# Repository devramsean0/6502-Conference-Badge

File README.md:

# 6502-Conference-Badge
A little 6502 flashy LED conference badge

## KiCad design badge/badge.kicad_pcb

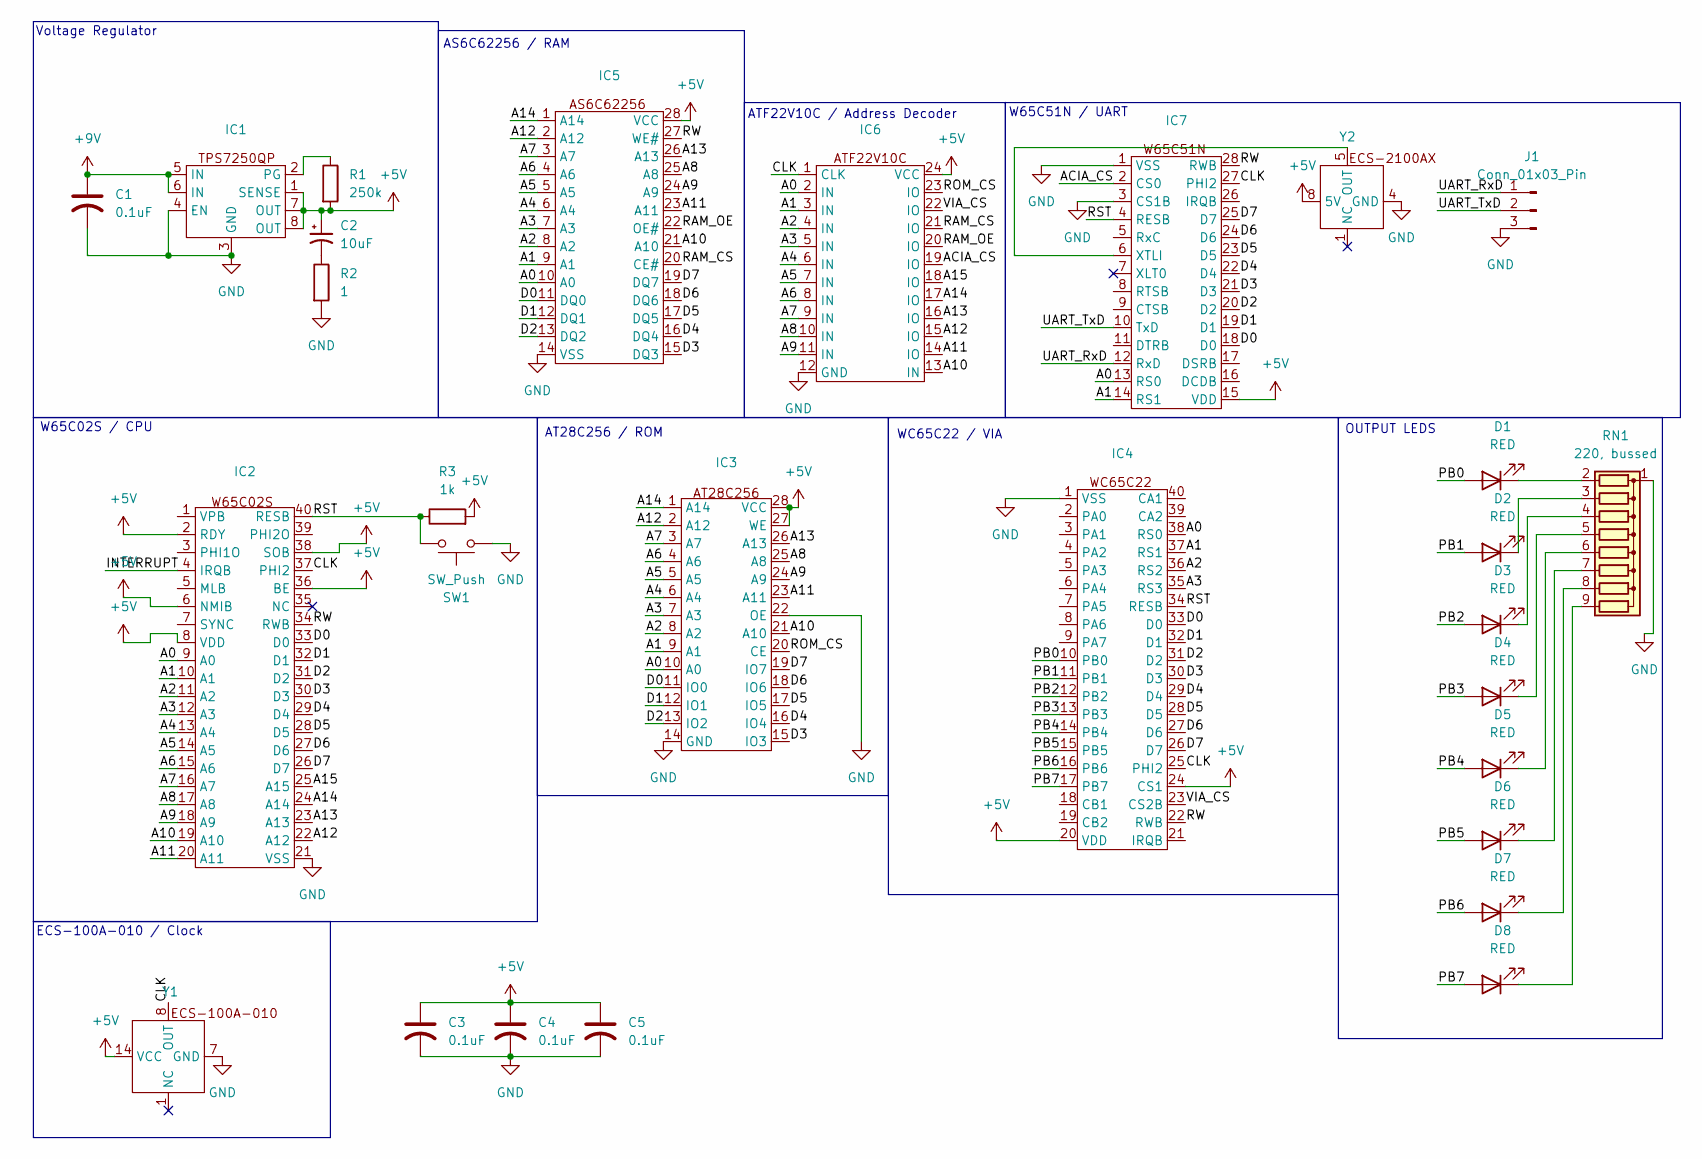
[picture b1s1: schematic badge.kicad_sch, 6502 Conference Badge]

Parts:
C1, C3, C4, C5: 0.1uF; CP_Radial_Tantal_D5.5mm_P2.50mm
C2: 10uF; CP_Axial_L10.0mm_D6.0mm_P15.00mm_Horizontal
D1, D2, D3, D4, D5, D6, D7, D8: RED; LED_D5.0mm
IC1: DIP-8_W7.62mm_Socket
IC2, IC4: DIP-40_W15.24mm_Socket
IC3, IC5, IC7: DIP-28_W15.24mm_Socket
IC6: DIP-24_W7.62mm_Socket
J1: Conn_01x03_Pin; PinHeader_1x03_P2.54mm_Vertical
R1: 250k; R_Axial_DIN0411_L9.9mm_D3.6mm_P7.62mm_Vertical
R2: 1; R_Axial_DIN0516_L15.5mm_D5.0mm_P20.32mm_Horizontal
R3: 1k; R_Axial_DIN0309_L9.0mm_D3.2mm_P12.70mm_Horizontal
RN1: 220, bussed; R_Array_SIP9
SW1: SW_Push; SW_PUSH_6mm
Y1: ECS100A010
Y2: ECS2100AX18432MHZ

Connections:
+9V: C1.1, IC1.5 (IN), IC1.6 (IN)
/A0: IC2.9 (A0), IC3.10 (A0), IC4.38 (RS0), IC5.10 (A0), IC6.2 (IN), IC7.13 (RS0)
/A1: IC2.10 (A1), IC3.9 (A1), IC4.37 (RS1), IC5.9 (A1), IC6.3 (IN), IC7.14 (RS1)
/A2: IC2.11 (A2), IC3.8 (A2), IC4.36 (RS2), IC5.8 (A2), IC6.4 (IN)
/A3: IC2.12 (A3), IC3.7 (A3), IC4.35 (RS3), IC5.7 (A3), IC6.5 (IN)
/A4: IC2.13 (A4), IC3.6 (A4), IC5.6 (A4), IC6.6 (IN)
/A5: IC2.14 (A5), IC3.5 (A5), IC5.5 (A5), IC6.7 (IN)
/A6: IC2.15 (A6), IC3.4 (A6), IC5.4 (A6), IC6.8 (IN)
/A7: IC2.16 (A7), IC3.3 (A7), IC5.3 (A7), IC6.9 (IN)
/A8: IC2.17 (A8), IC3.25 (A8), IC5.25 (A8), IC6.10 (IN)
/A9: IC2.18 (A9), IC3.24 (A9), IC5.24 (A9), IC6.11 (IN)
/A10: IC2.19 (A10), IC3.21 (A10), IC5.21 (A10), IC6.13 (IN)
/A11: IC2.20 (A11), IC3.23 (A11), IC5.23 (A11), IC6.14 (IO)
/A12: IC2.22 (A12), IC3.2 (A12), IC5.2 (A12), IC6.15 (IO)
/A14: IC2.24 (A14), IC3.1 (A14), IC5.1 (A14), IC6.17 (IO)
/A15: IC2.25 (A15), IC6.18 (IO)
/ACIA_CS: IC6.19 (IO), IC7.2 (CS0)
/CLK: IC2.37 (PHI2), IC4.25 (PHI2), IC6.1 (CLK), IC7.27 (PHI2), Y1.8 (OUT)
/D0: IC2.33 (D0), IC3.11 (IO0), IC4.33 (D0), IC5.11 (DQ0), IC7.18 (D0)
/D1: IC2.32 (D1), IC3.12 (IO1), IC4.32 (D1), IC5.12 (DQ1), IC7.19 (D1)
/D2: IC2.31 (D2), IC3.13 (IO2), IC4.31 (D2), IC5.13 (DQ2), IC7.20 (D2)
/D3: IC2.30 (D3), IC3.15 (IO3), IC4.30 (D3), IC5.15 (DQ3), IC7.21 (D3)
/D4: IC2.29 (D4), IC3.16 (IO4), IC4.29 (D4), IC5.16 (DQ4), IC7.22 (D4)
/D5: IC2.28 (D5), IC3.17 (IO5), IC4.28 (D5), IC5.17 (DQ5), IC7.23 (D5)
/D6: IC2.27 (D6), IC3.18 (IO6), IC4.27 (D6), IC5.18 (DQ6), IC7.24 (D6)
/D7: IC2.26 (D7), IC3.19 (IO7), IC4.26 (D7), IC5.19 (DQ7), IC7.25 (D7)
/INTERRUPT: IC2.4 (IRQB)
/PB0: D1.2 (A), IC4.10 (PB0)
/PB1: D2.2 (A), IC4.11 (PB1)
/PB2: D3.2 (A), IC4.12 (PB2)
/PB3: D4.2 (A), IC4.13 (PB3)
/PB4: D5.2 (A), IC4.14 (PB4)
/PB5: D6.2 (A), IC4.15 (PB5)
/PB6: D7.2 (A), IC4.16 (PB6)
/PB7: D8.2 (A), IC4.17 (PB7)
/RAM_CS: IC5.20 (CE#), IC6.21 (IO)
/RAM_OE: IC5.22 (OE#), IC6.20 (IO)
/ROM_CS: IC3.20 (CE), IC6.23 (IO)
/RST: IC2.40 (RESB), IC4.34 (RESB), IC7.4 (RESB), R3.1, SW1.1
/RW: IC2.34 (RWB), IC4.22 (RWB), IC5.27 (WE#), IC7.28 (RWB)
/UART_RxD: IC7.12 (RxD), J1.1
/UART_TxD: IC7.10 (TxD), J1.2
/VIA_CS: IC4.23 (CS2B), IC6.22 (IO)
GND: C1.2, C3.2, C4.2, C5.2, IC1.3 (GND), IC1.4 (EN), IC2.21 (VSS), IC3.14 (GND), IC3.22 (OE), IC4.1 (VSS), IC5.14 (VSS), IC6.12 (GND), IC7.1 (VSS), IC7.3 (CS1B), J1.3, R2.2, RN1.1 (common), SW1.2, Y1.7 (GND), Y2.4 (GND)
unnamed: C2.2, R2.1
unnamed: D1.1 (K), RN1.2 (R1)
unnamed: D2.1 (K), RN1.3 (R2)
unnamed: D3.1 (K), RN1.4 (R3)
unnamed: D4.1 (K), RN1.5 (R4)
unnamed: D5.1 (K), RN1.6 (R5)
unnamed: D6.1 (K), RN1.7 (R6)
unnamed: D7.1 (K), RN1.8 (R7)
unnamed: D8.1 (K), RN1.9 (R8)
unnamed: IC1.2 (PG), R1.1
unnamed: IC7.6 (XTLI), Y2.5 (OUT)

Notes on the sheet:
ATF22V10C / Address Decoder
W65C51N / UART
AT28C256 / ROM
ECS-100A-010 / Clock
WC65C22 / VIA
OUTPUT LEDS
AS6C62256 / RAM
Voltage Regulator
W65C02S / CPU

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
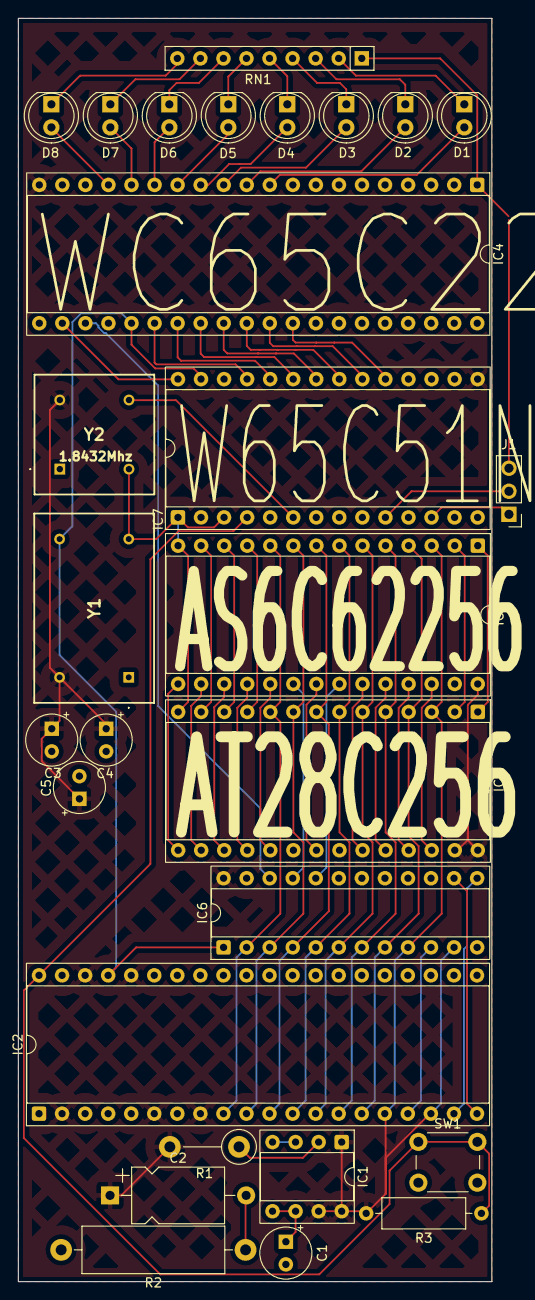
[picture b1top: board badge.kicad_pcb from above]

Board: 2 copper layers, 52.2 x 139.2 mm, 28 parts (0 on the bottom side), 56 nets.

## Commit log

2025-06-30 Add most broken images to journal
2025-07-01 Continue work + add a datasheet
2025-07-01 Start on actual layout
2025-07-02 Add core 6502 Wiring
2025-07-02 Make the voltage regulator look nice
2025-07-02 Add ROM
2025-07-02 VIA design work and Progress Check
2025-07-02 Output LEDS
2025-07-02 Partially add RAM, and a fair amount of commentry about desires with the design
2025-07-03 Add some thoughts on the fundamentals
2025-07-03 Add the Address Decoding PLD
2025-07-04 Add UART serial
2025-07-04 Add clock and some notes about a USB to UART adapter
2025-07-04 Add missing image
2025-07-04 [ImgBot] Optimize images
    *Total -- 3,444.69kb -> 2,937.68kb (14.72%)
    /Journal/Images/W65C02S-symbol.png -- 33.61kb -> 9.67kb (71.23%)
    /Journal/Images/ATF22V10C-symbol.png -- 21.15kb -> 6.52kb (69.16%)
    /Journal/Images/W65C51N-symbol.png -- 29.63kb -> 10.64kb (64.08%)
    /Journal/Images/ATF22V10C.png -- 34.88kb -> 14.57kb (58.24%)
    /Journal/Images/AS6C62256-symbol.png -- 13.72kb -> 5.86kb (57.26%)
2025-07-04 Add a few missing power connections, fix an image link and add a schematic plot
2025-07-04 Fix missing Interrupt connection
2025-07-05 Assign various footprints and fix a few issues
2025-07-06 Assign some footprints
2025-07-06 Fix journal images
2025-07-06 Layout outputs
2025-07-06 Some work on routing
